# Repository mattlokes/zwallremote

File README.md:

# zwallremote
zwallremote (Zigbee Wall Remote) is a device based on TI's CC2530 Zigbee Tranciever with built in 8051. Which allows you to reuse your existing light switches to control Tradfi, Hue or other Zigbee Light Link lights.

In fact it actaully acts as a small cheap zigbee remote for all sorts of diffrent uses. For my use case i use it to send commands to zigbee2mqtt which are passed onto HomeAssistant for controlling my Tradfri light network. However there is no reason you could not use it to turn your TV on play music on some smart speakers.

# Basics
After booting, the zwallremote polls once a second to detect the state of the screw terminal. If there is a change in state it will send a ZCL_TOGGLE_CMD to the co-ordinator, currently a fixed address in the firmware. I measured current use to be approximately 2uA so it should be capable of running for over 2 years on a single CR2032 coin cell (depending on how many times the light switch is used). 

# PCB

No known issues, worked first time with my cheap aliexpress CC2530 modules. Pretty Simple

# Firmware
You can either:
1. Can use precompiled binary in firmware/bin/
  - Will need to change the address of your co-ordinator (currently 0x0012_4B00_02C5_A0A6)
    - Line 2053 of the hex file, its reverse byte ordered, see https://imgur.com/1fYdB8f.
  - TODO give script for manipulate the hex file
  
2. Comple it yourself:
  - Will need IAR workbench 8051.
  - TI's Z-Stack Home 1.2.2a.44539.
  - The files are just modification to the SampleSwitch example application so just replace files as required.
  - Patience, Prayer and Screaming.
  
# Zigbee2mqtt changes (Now on mainline zigbee2mqtt)

1. You need to add ZWallRemote to "const devices" list of dictionaries in "node_modules/zigbee-shepherd-converters/devices.js":

```python
const devices = [
...
  {
      zigbeeModel: ['ZWallRemote0'],
      model: 'ZWallRemote0',
      vendor: 'Custom devices (DiY)',
      description: 'Matts Wall Switch Remote (https://github.com/mattlokes/ZWallRemote)'
      supports: 'on/off',
      fromZigbee: [ fz.cmdToggle ],
      toZigbee: [],
  },
...
]
```

2. Add "ZWallRemote0" to the "const mapping" dictionary in "lib/extension/homeassistant.js"

```python
const mapping = { 
 ...
    'ZWallRemote0': [ configurations.sensor_action ]
 ...
 }
```

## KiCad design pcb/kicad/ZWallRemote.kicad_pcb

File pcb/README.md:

The KiCad PCB uses a custom footprint i made for the SZ1v5 CC2530 module from aliexpress:

1. Add the follow footprint to "kicad/library/RF_Module.lib"

```
# SZ1v5
#
DEF SZ1v5 U 0 40 Y Y 1 F N
F0 "U" 0 -200 50 H V C CNN
F1 "SZ1v5" 0 150 50 H V C CNN
F2 "RF_Module:SZ1v5" 0 0 50 H V C CNN
F3 "" 0 -200 50 H I C CNN
DRAW
S 750 -650 -750 625 0 1 10 f
X GND 1 750 450 100 R 50 50 0 0 W
X P1_4 10 750 -450 100 R 50 50 0 0 B
X P1_3 11 750 -550 100 R 50 50 0 0 B
X P0_1 14 -750 350 100 L 50 50 0 0 B
X P0_2 15 -750 250 100 L 50 50 0 0 B
X P0_3 16 -750 150 100 L 50 50 0 0 B
X P0_4 17 -750 50 100 L 50 50 0 0 B
X P0_5 18 -750 -50 100 L 50 50 0 0 B
X P0_6 19 -750 -150 100 L 50 50 0 0 B
X 3V3 2 750 350 100 R 50 50 0 0 W
X P0_7 20 -750 -250 100 L 50 50 0 0 B
X P1_0 21 -750 -350 100 L 50 50 0 0 B
X P1_1 22 -750 -450 100 L 50 50 0 0 B
X P1_2 23 -750 -550 100 L 50 50 0 0 B
X 3V3 3 750 250 100 R 50 50 0 0 W
X P2_2 4 750 150 100 R 50 50 0 0 B
X P2_1 5 750 50 100 R 50 50 0 0 B
X P2_0 6 750 -50 100 R 50 50 0 0 B
X P1_7 7 750 -150 100 R 50 50 0 0 B
X P1_6 8 750 -250 100 R 50 50 0 0 B
X P1_5 9 750 -350 100 R 50 50 0 0 B
X GND 0 750 550 100 R 50 50 1 1 W
X RST_N 12 -750 550 100 L 50 50 1 1 I
X P0_0 13 -750 450 100 L 50 50 1 1 B
ENDDRAW
ENDDEF
```
2. Add the footprint description to "kicad/library/RF_Module.dcm"

```
$CMP SZ1v5
D cc2530 Zigbee Module
$ENDCMP
```

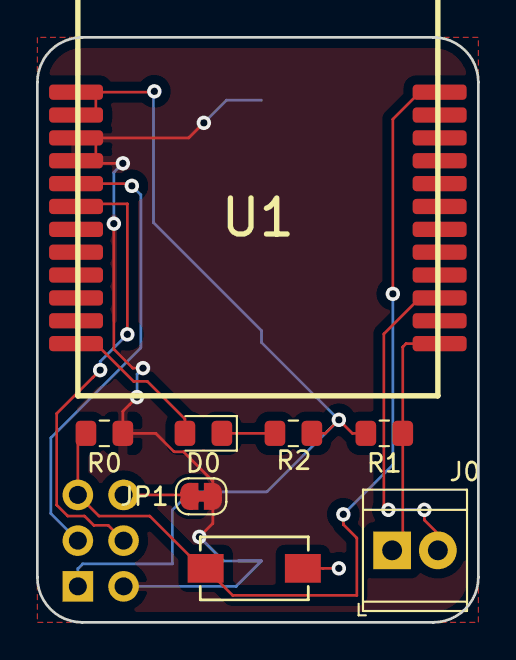
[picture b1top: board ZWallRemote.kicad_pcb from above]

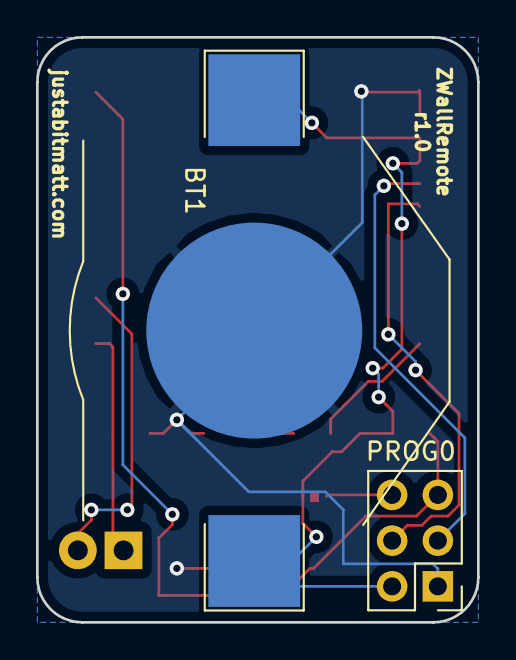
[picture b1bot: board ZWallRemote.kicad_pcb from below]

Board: 2 copper layers, 24.5 x 32.5 mm, 10 parts (2 on the bottom side), 10 nets.

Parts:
BT1: Battery_Cell; BatteryHolder_Keystone_3002_1x2032
D0: STATUS; LED_0805_2012Metric_Pad1.15x1.40mm_HandSolder
J0: SWITCH; TerminalBlock_TE_282834-2_1x02_P2.54mm_Horizontal
JP1: Jumper_NO_Small; SolderJumper-2_P1.3mm_Bridged_RoundedPad1.0x1.5mm
PROG0: Conn_02x03_Odd_Even; PinHeader_2x03_P2.54mm_Vertical
R0: 10k; R_0805_2012Metric_Pad1.15x1.40mm_HandSolder
R1: 1M; R_0805_2012Metric_Pad1.15x1.40mm_HandSolder
R2: 47; R_0805_2012Metric_Pad1.15x1.40mm_HandSolder
SW0: RESET_SW; DTSM-32S-B
U1: SZ1v5

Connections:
+3V0: BT1.1, JP1.2, PROG0.2, R0.1, U1.2, U1.3
DBG_CLK: PROG0.3, U1.4
DBG_DATA: PROG0.4, U1.5
GND: BT1.2, PROG0.1, R1.2, R2.2, SW0.2, U1.0, U1.1
unnamed: D0.1, R2.1
unnamed: JP1.1, PROG0.6
RESET_N: PROG0.5, R0.2, SW0.1, U1.12
STATUS: D0.2, U1.11
SW_EN: J0.2, U1.21
SW_READ: J0.1, R1.1, U1.23

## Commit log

2019-09-30 Directory Structure
2019-09-30 Rename OSAL_SampleSw.c to firmware/src/OSAL_SampleSw.c
2019-09-30 Rename ZWallRemote_v0_1.hex to firmware/bin/ZWallRemote_v0_1.hex
2019-09-30 Rename zcl_samplesw.c to firmware/src/zcl_samplesw.c
2019-09-30 Rename zcl_samplesw.h to firmware/src/zcl_samplesw.h
2019-09-30 Rename zcl_samplesw_data.c to firmware/src/zcl_samplesw_data.c
2020-07-15 Script to set coordinator address in firmware
    Script to set coordinator address in firmware
